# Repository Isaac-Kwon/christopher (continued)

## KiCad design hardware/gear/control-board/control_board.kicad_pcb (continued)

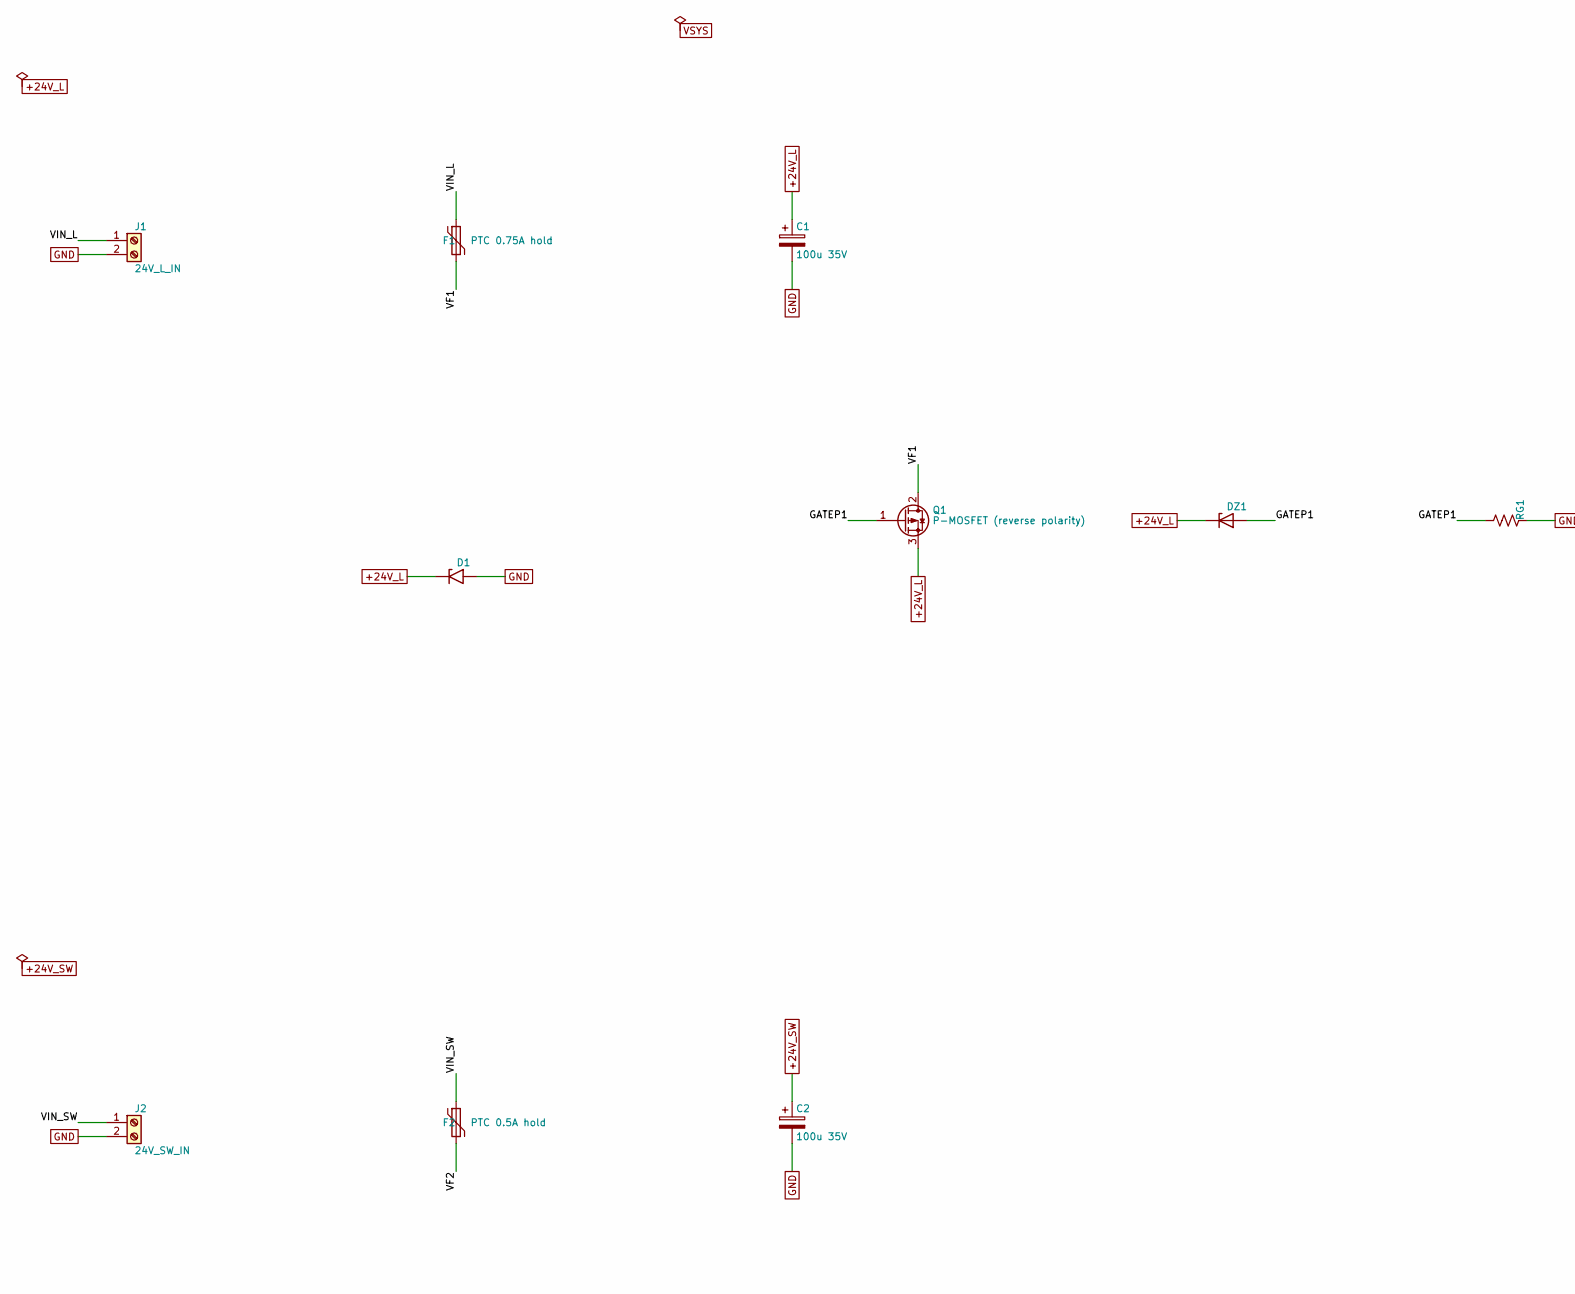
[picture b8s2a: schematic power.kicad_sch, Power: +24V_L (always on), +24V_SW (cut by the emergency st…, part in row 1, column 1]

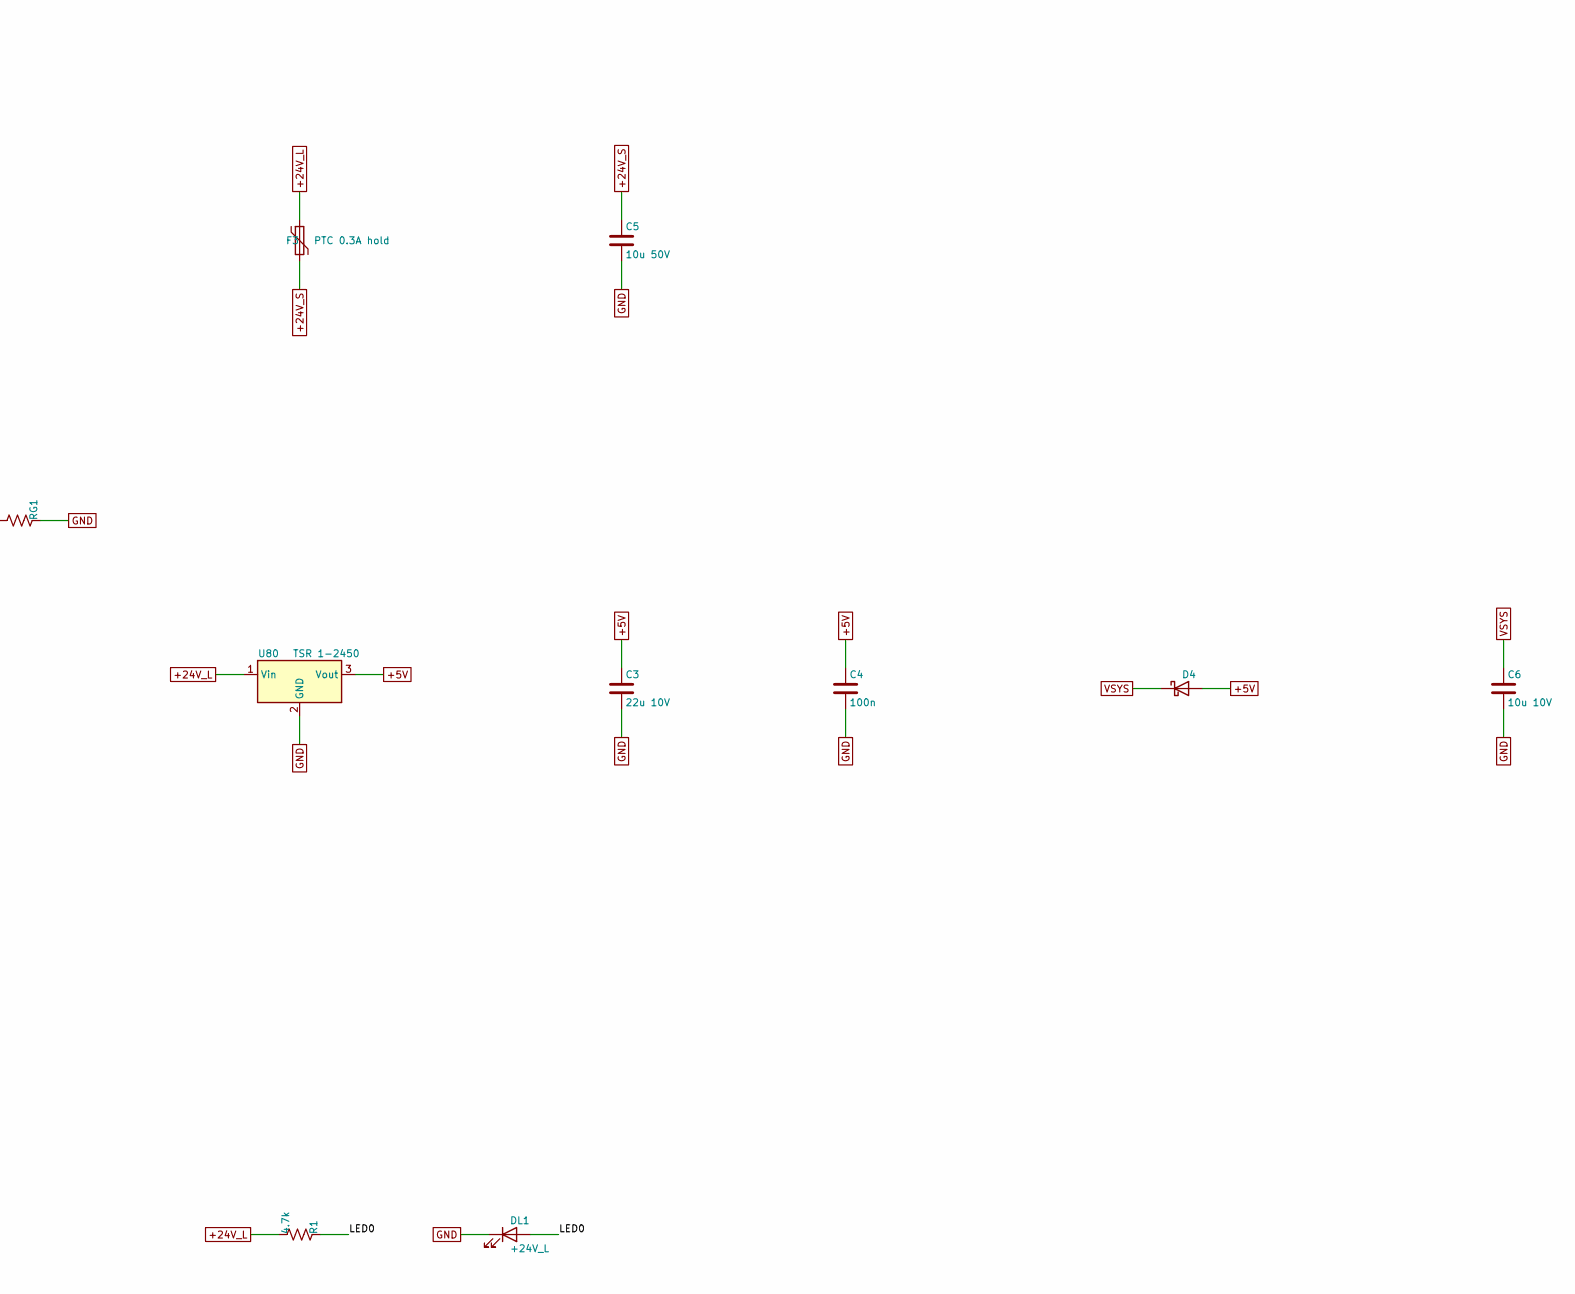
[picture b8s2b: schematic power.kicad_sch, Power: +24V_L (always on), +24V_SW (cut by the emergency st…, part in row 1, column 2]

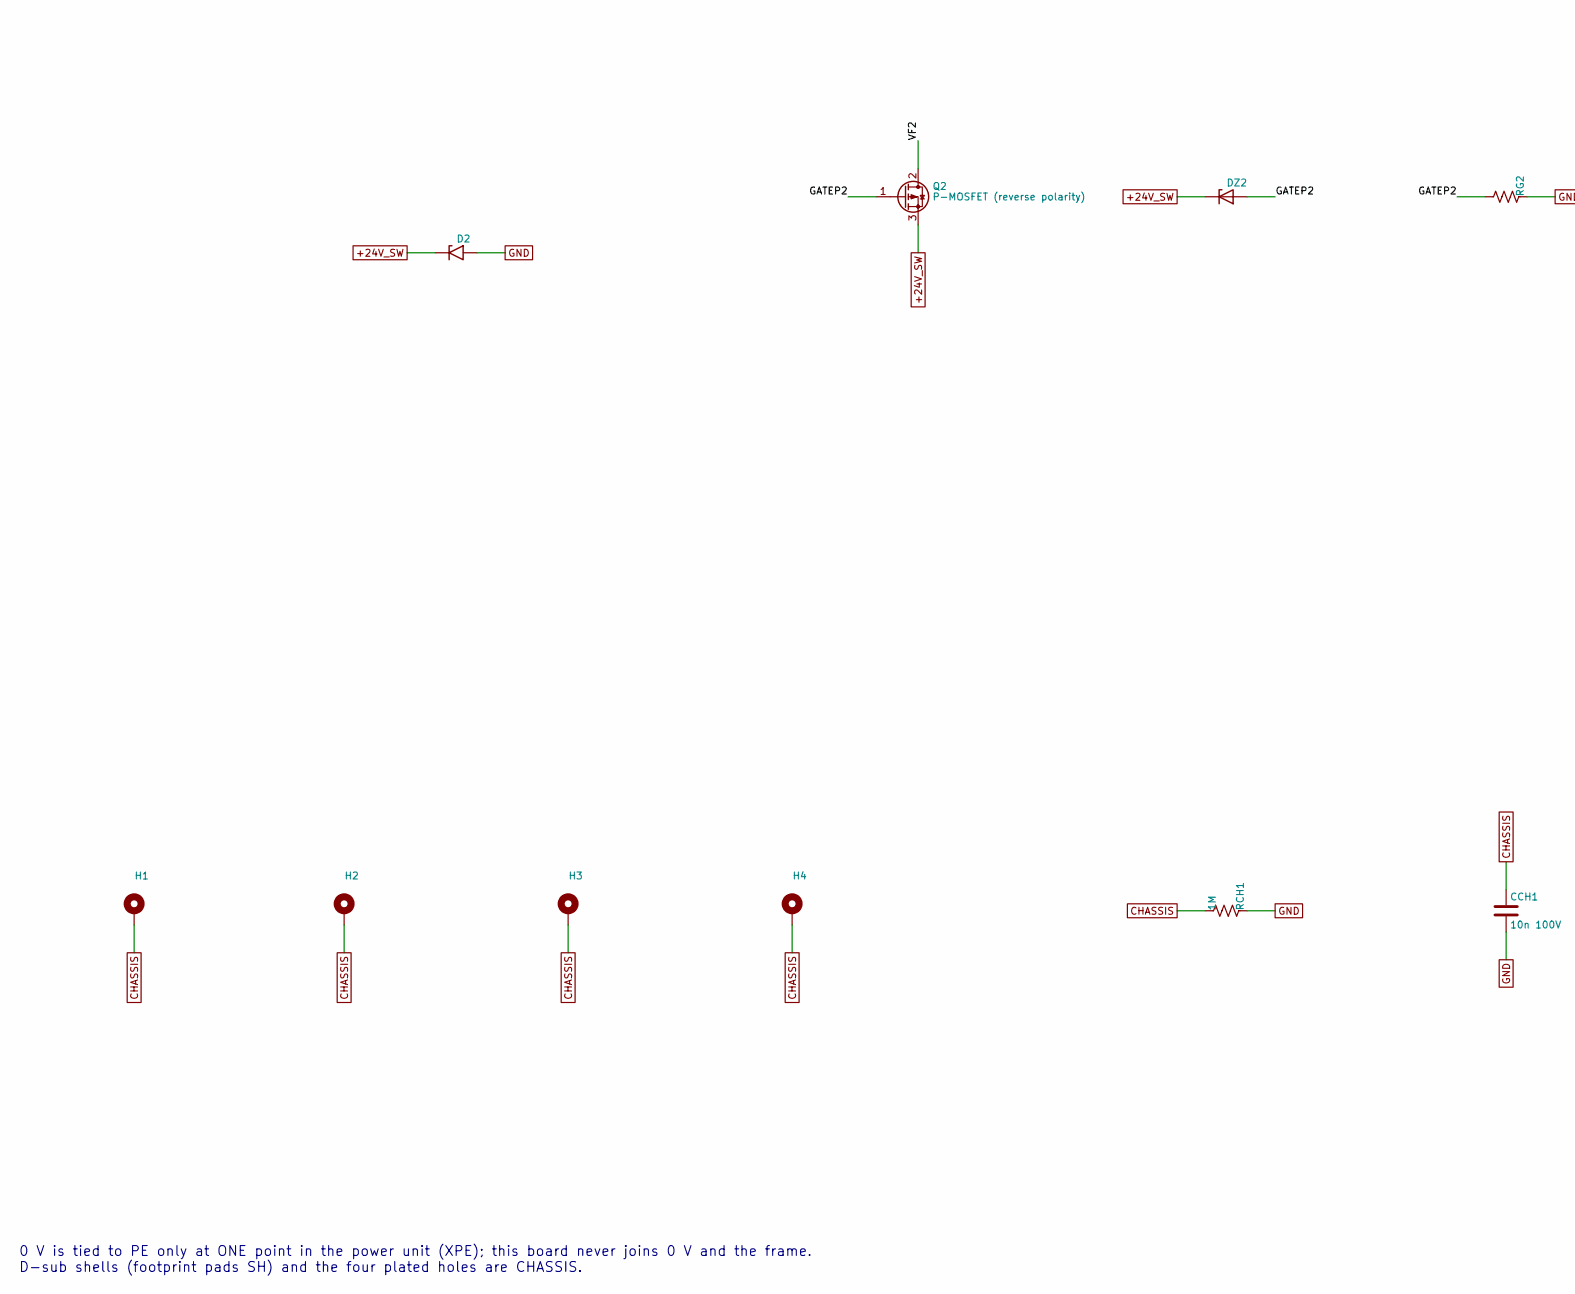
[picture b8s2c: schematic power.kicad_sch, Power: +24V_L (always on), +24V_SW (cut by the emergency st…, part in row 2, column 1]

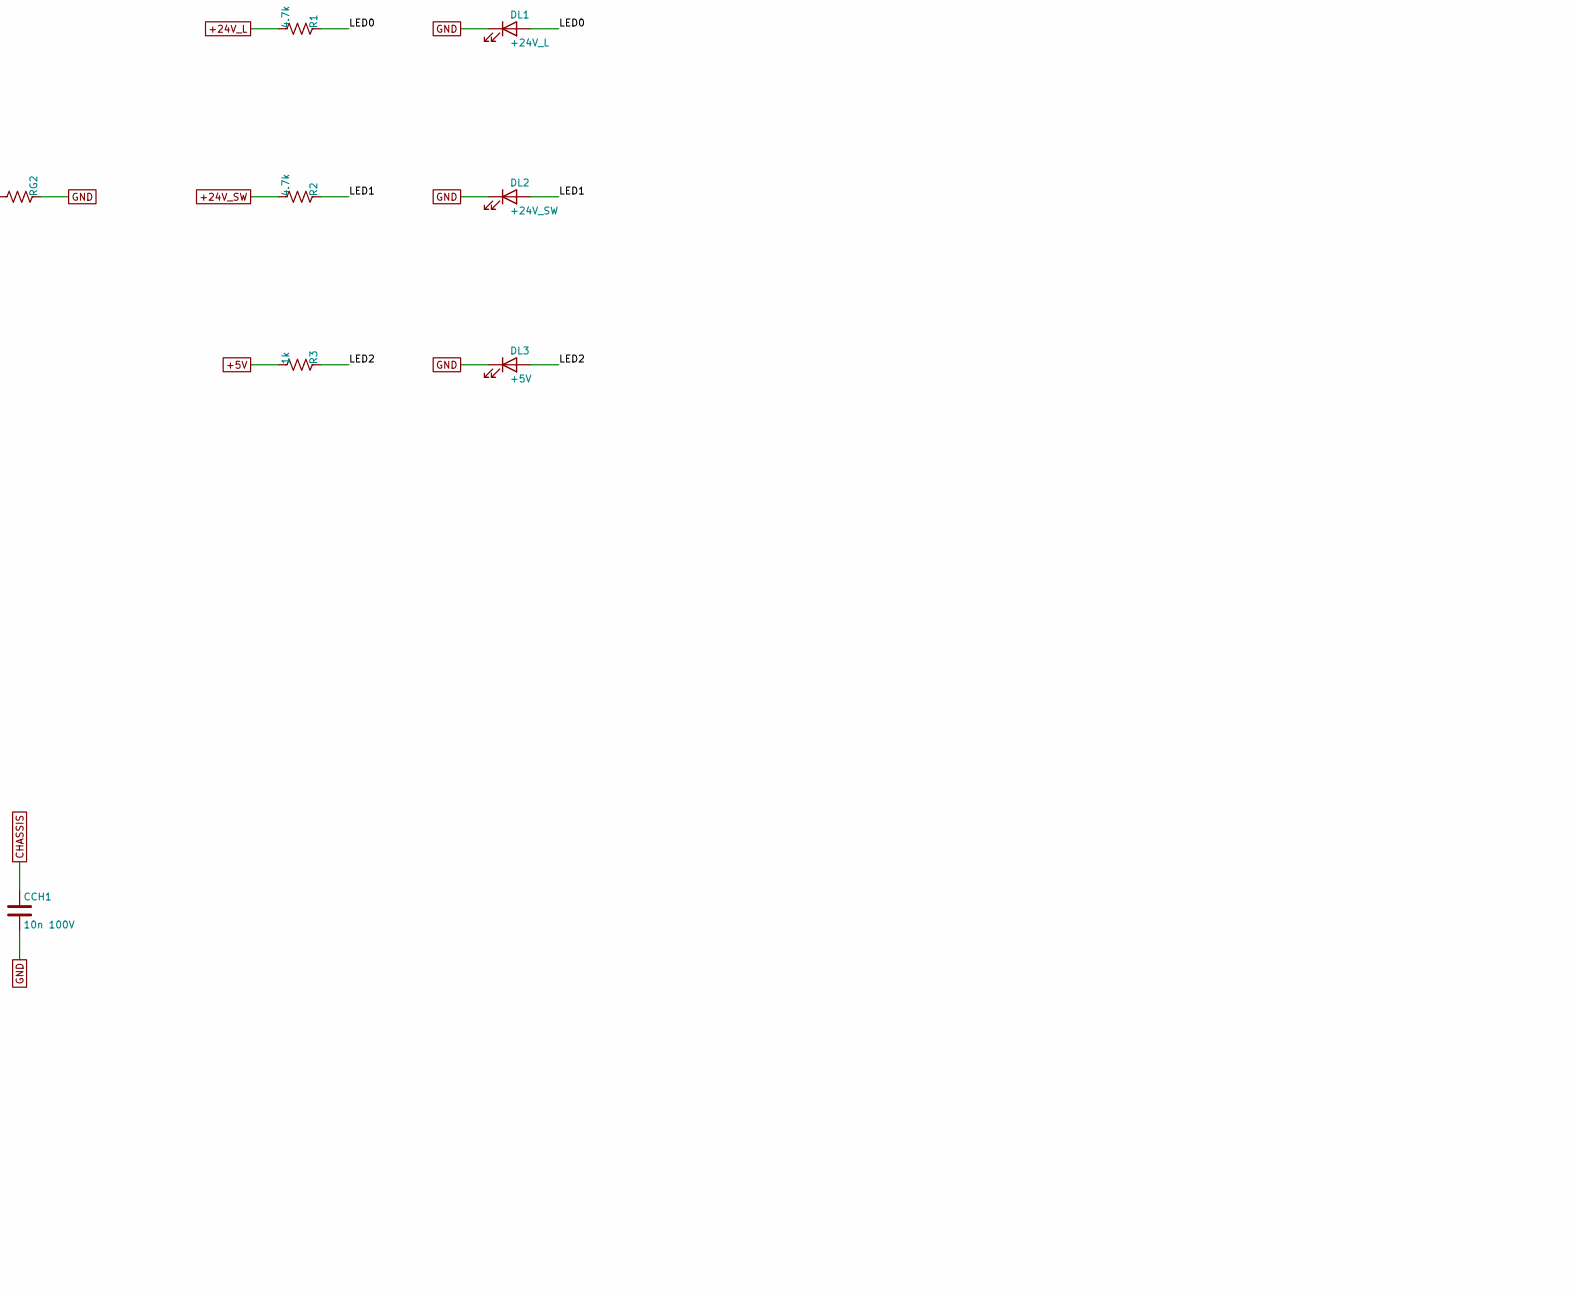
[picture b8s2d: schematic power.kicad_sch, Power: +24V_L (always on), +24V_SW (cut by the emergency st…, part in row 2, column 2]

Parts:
C1, C2: 100u 35V; CP_Elec_8x10
C3: 22u 10V; C_1206_3216Metric
C4: 100n; C_0603_1608Metric
C5: 10u 50V; C_1206_3216Metric
C6: 10u 10V; C_0805_2012Metric
CCH1: 10n 100V; C_0603_1608Metric
D1, D2: SMAJ33A; D_SMA
D4: SS14; D_SOD-123
DL1: +24V_L; LED_0603_1608Metric
DL2: +24V_SW; LED_0603_1608Metric
DL3: +5V; LED_0603_1608Metric
DZ1, DZ2: 12V; D_SOD-123
F1: PTC 0.75A hold; Fuse_1812_4532Metric
F2: PTC 0.5A hold; Fuse_1812_4532Metric
F3: PTC 0.3A hold; Fuse_1206_3216Metric
H1, H2, H3, H4: MountingHole_Pad; MountingHole_3.2mm_M3_Pad
J1: 24V_L_IN; TerminalBlock_Phoenix_MKDS-1,5-2-5.08_1x02_P5.08mm_Horizont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
J2: 24V_SW_IN; TerminalBlock_Phoenix_MKDS-1,5-2-5.08_1x02_P5.08mm_Horizont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
Q1, Q2: P-MOSFET (reverse polarity); SOT-223-3_TabPin2
R1, R2: 4.7k; R_0603_1608Metric
R3: 1k; R_0603_1608Metric
RCH1: 1M; R_0603_1608Metric
RG1, RG2: 100k; R_0603_1608Metric
U80: TSR 1-2450; Converter_DCDC_TRACO_TSR-1_THT

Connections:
+5V: C3.1, C4.1, D4.2 (A), R3.1, U80.3 (Vout)
+24V_L: C1.1, D1.1 (A1), DZ1.1 (K), F3.1, Q1.3 (S), R1.1, U80.1 (Vin); also elsewhere on the board
+24V_S: C5.1, F3.2; also elsewhere on the board
+24V_SW: C2.1, D2.1 (A1), DZ2.1 (K), Q2.3 (S), R2.1; also elsewhere on the board
/POWER/GATEP1: DZ1.2 (A), Q1.1 (G), RG1.1
/POWER/GATEP2: DZ2.2 (A), Q2.1 (G), RG2.1
/POWER/LED0: DL1.2 (A), R1.2
/POWER/LED1: DL2.2 (A), R2.2
/POWER/LED2: DL3.2 (A), R3.2
/POWER/VF1: F1.2, Q1.2 (D)
/POWER/VF2: F2.2, Q2.2 (D)
/POWER/VIN_L: F1.1, J1.1
/POWER/VIN_SW: F2.1, J2.1
CHASSIS: CCH1.1, H1.1, H2.1, H3.1, H4.1, RCH1.1; also elsewhere on the board
GND: C1.2, C2.2, C3.2, C4.2, C5.2, C6.2, CCH1.2, D1.2 (A2), D2.2 (A2), DL1.1 (K), DL2.1 (K), DL3.1 (K), J1.2, J2.2, RCH1.2, RG1.2, RG2.2, U80.2 (GND); also elsewhere on the board
VSYS: C6.1, D4.1 (K); also elsewhere on the board

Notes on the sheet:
0 V is tied to PE only at ONE point in the power unit (XPE); this board never joins 0 V and the frame. D-sub shells (footprint pads SH) and the four plated holes are CHASSIS.

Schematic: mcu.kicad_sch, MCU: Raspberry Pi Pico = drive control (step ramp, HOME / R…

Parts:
C10: 10u; C_0805_2012Metric
C11: 100n; C_0603_1608Metric
R10, R11, R12: 10k; R_0603_1608Metric
SW1: RESET; SW_SPST_PTS645Sx43SMTR92
U1: Raspberry Pi Pico; RaspberryPi_Pico_Common_THT

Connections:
+3V3: C10.1, C11.1, R11.2, R12.2, U1.36 (3V3); also elsewhere on the board
/MCU/RUN_PIN: SW1.1, U1.30 (RUN)
ALM_M: U1.17 (GPIO13); also elsewhere on the board
DIR_M: U1.2 (GPIO1); also elsewhere on the board
ENA_M: U1.4 (GPIO2); also elsewhere on the board
ESTOPOK_M: U1.20 (GPIO15); also elsewhere on the board
GND: C10.2, C11.2, R10.2, SW1.2, U1.3 (GND), U1.8 (GND), U1.13 (GND), U1.18 (GND), U1.23 (GND), U1.28 (GND), U1.38 (GND); also elsewhere on the board
HOME_M: U1.15 (GPIO11); also elsewhere on the board
HOMING: R11.1, U1.6 (GPIO4); also elsewhere on the board
ILOCKOK_M: U1.21 (GPIO16); also elsewhere on the board
I_L: U1.27 (GPIO21); also elsewhere on the board
I_M: U1.31 (GPIO26_ADC0); also elsewhere on the board
I_S: U1.34 (GPIO28_ADC2); also elsewhere on the board
MOSI_M: U1.9 (GPIO6); also elsewhere on the board
OE_M: R12.1, U1.11 (GPIO8); also elsewhere on the board
PUL_M: U1.1 (GPIO0); also elsewhere on the board
RCLK_M: U1.10 (GPIO7); also elsewhere on the board
RUN_M: U1.12 (GPIO9); also elsewhere on the board
SCK_M: U1.7 (GPIO5); also elsewhere on the board
SLOT_C: U1.25 (GPIO19); also elsewhere on the board
SLOT_J: U1.24 (GPIO18); also elsewhere on the board
SLOT_S: U1.22 (GPIO17); also elsewhere on the board
STOPL_M: U1.14 (GPIO10); also elsewhere on the board
SW_M: U1.19 (GPIO14); also elsewhere on the board
TXEN: R10.1, U1.5 (GPIO3); also elsewhere on the board
T_L: U1.26 (GPIO20); also elsewhere on the board
T_M: U1.29 (GPIO22); also elsewhere on the board
T_S: U1.32 (GPIO27_ADC1); also elsewhere on the board
V48_M: U1.16 (GPIO12); also elsewhere on the board
VSYS: U1.39 (VSYS); also elsewhere on the board

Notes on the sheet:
GP0 PUL GP1 DIR GP2 ENA (-> TBD62783A U60 -> 1.5k -> J_DRV) GP3 TXEN GP4 HOMING (-> LOGIC) GP5 SCK GP6 MOSI GP7 RCLK GP8 /OE -> 3 x 74HC595 (STOPPED, AT_HOME, END, POS0-14) GP9-16 RUN, STOP_LATCH, HOME, V48_OK, DRV_ALM, SW_OK, ESTOP_OK, ILOCK_OK (optocoupler outputs) GP17-19 conditioned slot levels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

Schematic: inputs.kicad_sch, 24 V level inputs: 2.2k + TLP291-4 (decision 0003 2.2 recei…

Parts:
D20, D21, D22, D23, D24, D25, D26, D27: 1N4148W; D_SOD-123
R20, R21, R22, R23, R24, R25, R26, R27: 2.2k; R_0603_1608Metric
R28: 4.7k; R_0603_1608Metric
R30, R31, R32, R33, R34, R35, R36, R37: 10k; R_0603_1608Metric
U40, U41: TLP291-4; SOIC-16_4.55x10.3mm_P1.27mm

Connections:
+3V3: U40.10, U40.12, U40.14, U40.16, U41.10, U41.12, U41.14, U41.16; also elsewhere on the board
+24V_L: R28.1; also elsewhere on the board
+24V_SW: R26.1; also elsewhere on the board
/INPUTS/SNS_ALM: D27.1 (K), R27.2, U41.7
/INPUTS/SNS_ESTOP_RET: D23.1 (K), R23.2, U40.7
/INPUTS/SNS_HOME: D22.1 (K), R22.2, U40.5
/INPUTS/SNS_ILOCK_RET: D24.1 (K), R24.2, U41.1
/INPUTS/SNS_RUN: D20.1 (K), R20.2, U40.1
/INPUTS/SNS_STOP_LATCH: D21.1 (K), R21.2, U40.3
/INPUTS/SNS_SW_OK: D26.1 (K), R26.2, U41.5
/INPUTS/SNS_V48_OK: D25.1 (K), R25.2, U41.3
ALM_IN: R27.1, R28.2; also elsewhere on the board
ALM_M: R37.1, U41.9; also elsewhere on the board
ESTOPOK_M: R33.1, U40.9; also elsewhere on the board
ESTOP_RET: R23.1; also elsewhere on the board
GND: D20.2 (A), D21.2 (A), D22.2 (A), D23.2 (A), D24.2 (A), D25.2 (A), D26.2 (A), D27.2 (A), R30.2, R31.2, R32.2, R33.2, R34.2, R35.2, R36.2, R37.2, U40.2, U40.4, U40.6, U40.8, U41.2, U41.4, U41.6, U41.8; also elsewhere on the board
HOME: R22.1; also elsewhere on the board
HOME_M: R32.1, U40.11; also elsewhere on the board
ILOCKOK_M: R34.1, U41.15; also elsewhere on the board
ILOCK_RET: R24.1; also elsewhere on the board
RUN: R20.1; also elsewhere on the board
RUN_M: R30.1, U40.15; also elsewhere on the board
STOPL_M: R31.1, U40.13; also elsewhere on the board
STOP_LATCH: R21.1; also elsewhere on the board
SW_M: R36.1, U41.11; also elsewhere on the board
V48_M: R35.1, U41.13; also elsewhere on the board
V48_OK: R25.1; also elsewhere on the board

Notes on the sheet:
Polarity: *_M = 1 when the 24 V input is high. ALM_M = 1 means the drive output is OPEN (alarm / drive unpowered). V48_OK: 24 V level from an a-type auxiliary contact of KM3 (the 48 V contactor); the power unit must supply it (open item).

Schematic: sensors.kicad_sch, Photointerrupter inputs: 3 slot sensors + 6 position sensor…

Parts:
C20, C21, C22, C23, C24, C25, C26, C27, C28: 4.7n; C_0603_1608Metric
J10: SENS_S; JST_XH_B3B-XH-A_1x03_P2.50mm_Vertical
J11: SENS_J; JST_XH_B3B-XH-A_1x03_P2.50mm_Vertical
J12: SENS_C; JST_XH_B3B-XH-A_1x03_P2.50mm_Vertical
J13: SENS_TL; JST_XH_B3B-XH-A_1x03_P2.50mm_Vertical
J14: SENS_IL; JST_XH_B3B-XH-A_1x03_P2.50mm_Vertical
J15: SENS_TM; JST_XH_B3B-XH-A_1x03_P2.50mm_Vertical
J16: SENS_IM; JST_XH_B3B-XH-A_1x03_P2.50mm_Vertical
J17: SENS_TS; JST_XH_B3B-XH-A_1x03_P2.50mm_Vertical
J18: SENS_IS; JST_XH_B3B-XH-A_1x03_P2.50mm_Vertical
R40, R41, R42, R43, R44, R45, R46, R47, R48: 4.7k; R_0603_1608Metric
R50, R51, R52, R53, R54, R55, R56, R57, R58: 1k; R_0603_1608Metric

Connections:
+3V3: R40.1, R41.1, R42.1, R43.1, R44.1, R45.1, R46.1, R47.1, R48.1; also elsewhere on the board
+24V_S: J10.1, J11.1, J12.1, J13.1, J14.1, J15.1, J16.1, J17.1, J18.1; also elsewhere on the board
/SENSORS/RAW_C: J12.2, R42.2, R52.1
/SENSORS/RAW_IL: J14.2, R44.2, R54.1
/SENSORS/RAW_IM: J16.2, R46.2, R56.1
/SENSORS/RAW_IS: J18.2, R48.2, R58.1
/SENSORS/RAW_J: J11.2, R41.2, R51.1
/SENSORS/RAW_S: J10.2, R40.2, R50.1
/SENSORS/RAW_TL: J13.2, R43.2, R53.1
/SENSORS/RAW_TM: J15.2, R45.2, R55.1
/SENSORS/RAW_TS: J17.2, R47.2, R57.1
FLT_C: C22.1, R52.2; also elsewhere on the board
FLT_IL: C24.1, R54.2; also elsewhere on the board
FLT_IM: C26.1, R56.2; also elsewhere on the board
FLT_IS: C28.1, R58.2; also elsewhere on the board
FLT_J: C21.1, R51.2; also elsewhere on the board
FLT_S: C20.1, R50.2; also elsewhere on the board
FLT_TL: C23.1, R53.2; also elsewhere on the board
FLT_TM: C25.1, R55.2; also elsewhere on the board
FLT_TS: C27.1, R57.2; also elsewhere on the board
GND: C20.2, C21.2, C22.2, C23.2, C24.2, C25.2, C26.2, C27.2, C28.2, J10.3, J11.3, J12.3, J13.3, J14.3, J15.3, J16.3, J17.3, J18.3; also elsewhere on the board

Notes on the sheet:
Slot windows (connector face, layout.md 3.8, CAD params.SLOT_STEPS): STROBE -2.50..+4.52 ms, JUDGE +8.56..+16.63, CLEAR +18.65..+31.73 at 60 rpm. STROBE calibration = rotating bracket of the STROBE sensor (decision 0002); nothing on the board.

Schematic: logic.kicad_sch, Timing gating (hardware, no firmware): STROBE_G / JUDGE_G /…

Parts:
C40, C41, C42, C43, C44, C45, C46, C47, C50: 100n; C_0603_1608Metric
C51: 10n; C_0603_1608Metric
R60: 100k; R_0603_1608Metric
R61: 47k; R_0603_1608Metric
U30, U31, U32: 74HC14; SOIC-14_3.9x8.7mm_P1.27mm
U33, U34: 74HC08; SOIC-14_3.9x8.7mm_P1.27mm
U35: 74HC32; SOIC-14_3.9x8.7mm_P1.27mm
U36: 74HC02; SOIC-14_3.9x8.7mm_P1.27mm
U37: 74HC74; SOIC-14_3.9x8.7mm_P1.27mm

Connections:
+3V3: C40.1, C41.1, C42.1, C43.1, C44.1, C45.1, C46.1, C47.1, R60.1, U30.14 (VCC), U31.14 (VCC), U32.14 (VCC), U33.14 (VCC), U34.14 (VCC), U35.14 (VCC), U36.14 (VCC), U37.2 (D), U37.4 (~S), U37.14 (VCC); also elsewhere on the board
CLEAR_G: U32.1, U33.6; also elsewhere on the board
CLR1: U35.6, U36.2, U36.5, U36.6
CLRN: U32.2, U37.11 (C)
CYC: U35.2, U37.9 (Q)
CYC_R_N: U36.4, U37.13 (~R)
FLT_C: U30.5; also elsewhere on the board
FLT_IL: U30.11; also elsewhere on the board
FLT_IM: U31.1; also elsewhere on the board
FLT_IS: U31.5; also elsewhere on the board
FLT_J: U30.3; also elsewhere on the board
FLT_S: U30.1; also elsewhere on the board
FLT_TL: U30.9; also elsewhere on the board
FLT_TM: U30.13; also elsewhere on the board
FLT_TS: U31.3; also elsewhere on the board
GND: C40.2, C41.2, C42.2, C43.2, C44.2, C45.2, C46.2, C47.2, C50.2, C51.2, U30.7 (GND), U31.7 (GND), U32.5, U32.7 (GND), U32.9, U32.11, U32.13, U33.7 (GND), U34.4, U34.5, U34.7 (GND), U34.9, U34.10, U34.12, U34.13, U35.7 (GND), U35.9, U35.10, U35.12, U35.13, U36.7 (GND), U36.8, U36.9, U36.11, U36.12, U37.7 (GND), U37.12 (D); also elsewhere on the board
HOMING: U35.5; also elsewhere on the board
I_L: U30.10; also elsewhere on the board
I_M: U31.2; also elsewhere on the board
I_S: U31.6; also elsewhere on the board
JUDGE_G: U33.11; also elsewhere on the board
JUDGE_X: U33.8, U33.12
POR: U31.12, U35.4
POR_RC: C50.1, R60.2, U31.13
SEEN: U33.10, U37.5 (Q)
SEEN_R_N: U36.1, U37.1 (~R)
SLOT_C: U30.6, U33.4; also elsewhere on the board
SLOT_J: U30.4, U33.9; also elsewhere on the board
SLOT_S: U30.2, U33.1; also elsewhere on the board
SL_D: C51.1, R61.2, U31.11
SL_DB: U31.10, U34.2
SL_N: R61.1, U31.8, U34.1
SL_PULSE: U34.3, U36.3
STOPL_M: U31.9; also elsewhere on the board
STROBE_G: U32.3, U33.3, U37.3 (C); also elsewhere on the board
STROBE_N: U32.4, U37.10 (~S)
TXE: U33.2, U33.5, U33.13, U35.3
TXEN: U35.1; also elsewhere on the board
T_L: U30.8; also elsewhere on the board
T_M: U30.12; also elsewhere on the board
T_S: U31.4; also elsewhere on the board

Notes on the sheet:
CYC ~S = STROBE_N (low while STROBE_G high), ~R = CYC_R_N = NOR(POR | HOMING) (power-up and HOME: a cycle cut by an emergency stop is dropped; the HOME flush CLEAR replaces its CLEAR), D = 0, clock = CLRN (rises when CLEAR_G falls). SEEN D = 1, clock = STROBE_G, ~R = SEEN_R_N = NOR(POR | HOMING, SL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

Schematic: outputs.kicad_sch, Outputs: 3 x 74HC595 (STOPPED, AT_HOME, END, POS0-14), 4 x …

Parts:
C60, C61, C62: 100n; C_0603_1608Metric
C70, C71, C72, C73: 100n 50V; C_0805_2012Metric
F20, F21, F22, F23, F24, F25, F26, F27, F28, F29, F30, F31, F32, F33, F34, F35, F36, F37, F38, F39, F40: PTC 30mA/100mA; Fuse_1206_3216Metric
R70, R71, R72, R73, R74, R75, R78, R79, R80, R81, R82, R83, R84, R85, R86, R87, R88, R89, R90, R91, R92, R93, R94, R95, R110, R111, R112, R113, R114, R115, R116, R117, R118, R119, R120, R121, R122, R123, R124, R125, R126, R127, R128, R129, R130: 47k; R_0603_1608Metric
R150, R151, R152: 1.5k; R_0603_1608Metric
U50, U51, U52: 74HC595; SOIC-16_3.9x9.9mm_P1.27mm
U60, U61, U62, U63: TBD62783APG; SOIC-18W_7.5x11.6mm_P1.27mm

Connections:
+3V3: C60.1, C61.1, C62.1, U50.10 (~SRCLR), U50.16 (VCC), U51.10 (~SRCLR), U51.16 (VCC), U52.10 (~SRCLR), U52.16 (VCC); also elsewhere on the board
+24V_L: C71.1, C72.1, C73.1, U61.9 (VCC), U62.9 (VCC), U63.9 (VCC); also elsewhere on the board
+24V_SW: C70.1, U60.9 (VCC); also elsewhere on the board
/OUTPUTS/CH0: U50.9 (QH'), U51.14 (SER)
/OUTPUTS/CH1: U51.9 (QH'), U52.14 (SER)
AT_HOME: F24.2, R114.1; also elsewhere on the board
BIT0: R78.1, U50.15 (QA), U61.1 (I1)
BIT1: R79.1, U50.1 (QB), U61.2 (I2)
BIT2: R80.1, U50.2 (QC), U61.3 (I3)
BIT3: R81.1, U50.3 (QD), U61.4 (I4)
BIT4: R82.1, U50.4 (QE), U61.5 (I5)
BIT5: R83.1, U50.5 (QF), U61.6 (I6)
BIT6: R84.1, U50.6 (QG), U61.7 (I7)
BIT7: R85.1, U50.7 (QH), U61.8 (I8)
BIT8: R86.1, U51.15 (QA), U62.1 (I1)
BIT9: R87.1, U51.1 (QB), U62.2 (I2)
BIT10: R88.1, U51.2 (QC), U62.3 (I3)
BIT11: R89.1, U51.3 (QD), U62.4 (I4)
BIT12: R90.1, U51.4 (QE), U62.5 (I5)
BIT13: R91.1, U51.5 (QF), U62.6 (I6)
BIT14: R92.1, U51.6 (QG), U62.7 (I7)
BIT15: R93.1, U51.7 (QH), U62.8 (I8)
BIT16: R94.1, U52.15 (QA), U63.1 (I1)
BIT17: R95.1, U52.1 (QB), U63.2 (I2)
CLEAR: F22.2, R112.1; also elsewhere on the board
CLEAR_G: R72.1, U60.3 (I3); also elsewhere on the board
DIR_M: R74.1, U60.5 (I5); also elsewhere on the board
DO_AT_HOME: F24.1, U61.17 (O2)
DO_CLEAR: F22.1, U60.16 (O3)
DO_DIR: R151.1, U60.14 (O5)
DO_ENA: R152.1, U60.13 (O6)
DO_END: F25.1, U61.16 (O3)
DO_JUDGE: F21.1, U60.17 (O2)
DO_POS0: F26.1, U61.15 (O4)
DO_POS1: F27.1, U61.14 (O5)
DO_POS2: F28.1, U61.13 (O6)
DO_POS3: F29.1, U61.12 (O7)
DO_POS4: F30.1, U61.11 (O8)
DO_POS5: F31.1, U62.18 (O1)
DO_POS6: F32.1, U62.17 (O2)
DO_POS7: F33.1, U62.16 (O3)
DO_POS8: F34.1, U62.15 (O4)
DO_POS9: F35.1, U62.14 (O5)
DO_POS10: F36.1, U62.13 (O6)
DO_POS11: F37.1, U62.12 (O7)
DO_POS12: F38.1, U62.11 (O8)
DO_POS13: F39.1, U63.18 (O1)
DO_POS14: F40.1, U63.17 (O2)
DO_PUL: R150.1, U60.15 (O4)
DO_STOPPED: F23.1, U61.18 (O1)
DO_STROBE: F20.1, U60.18 (O1)
DRV_DIR: R151.2; also elsewhere on the board
DRV_ENA: R152.2; also elsewhere on the board
DRV_PUL: R150.2; also elsewhere on the board
ENA_M: R75.1, U60.6 (I6); also elsewhere on the board
END: F25.2, R115.1; also elsewhere on the board
GND: C60.2, C61.2, C62.2, C70.2, C71.2, C72.2, C73.2, R70.2, R71.2, R72.2, R73.2, R74.2, R75.2, R78.2, R79.2, R80.2, R81.2, R82.2, R83.2, R84.2, R85.2, R86.2, R87.2, R88.2, R89.2, R90.2, R91.2, R92.2, R93.2, R94.2, R95.2, R110.2, R111.2, R112.2, R113.2, R114.2, R115.2, R116.2, R117.2, R118.2, R119.2, R120.2, R121.2, R122.2, R123.2, R124.2, R125.2, R126.2, R127.2, R128.2, R129.2, R130.2, U50.8 (GND), U51.8 (GND), U52.8 (GND), U60.7 (I7), U60.8 (I8), U60.10 (GND), U61.10 (GND), U62.10 (GND), U63.3 (I3), U63.4 (I4), U63.5 (I5), U63.6 (I6), U63.7 (I7), U63.8 (I8), U63.10 (GND); also elsewhere on the board
JUDGE: F21.2, R111.1; also elsewhere on the board
JUDGE_G: R71.1, U60.2 (I2); also elsewhere on the board
MOSI_M: U50.14 (SER); also elsewhere on the board
OE_M: U50.13 (~OE), U51.13 (~OE), U52.13 (~OE); also elsewhere on the board
POS0: F26.2, R116.1; also elsewhere on the board
POS1: F27.2, R117.1; also elsewhere on the board
POS2: F28.2, R118.1; also elsewhere on the board
POS3: F29.2, R119.1; also elsewhere on the board
POS4: F30.2, R120.1; also elsewhere on the board
POS5: F31.2, R121.1; also elsewhere on the board
POS6: F32.2, R122.1; also elsewhere on the board
POS7: F33.2, R123.1; also elsewhere on the board
POS8: F34.2, R124.1; also elsewhere on the board
POS9: F35.2, R125.1; also elsewhere on the board
POS10: F36.2, R126.1; also elsewhere on the board
POS11: F37.2, R127.1; also elsewhere on the board
POS12: F38.2, R128.1; also elsewhere on the board
POS13: F39.2, R129.1; also elsewhere on the board
POS14: F40.2, R130.1; also elsewhere on the board
PUL_M: R73.1, U60.4 (I4); also elsewhere on the board
RCLK_M: U50.12 (RCLK), U51.12 (RCLK), U52.12 (RCLK); also elsewhere on the board
SCK_M: U50.11 (SRCLK), U51.11 (SRCLK), U52.11 (SRCLK); also elsewhere on the board
STOPPED: F23.2, R113.1; also elsewhere on the board
STROBE: F20.2, R110.1; also elsewhere on the board
STROBE_G: R70.1, U60.1 (I1); also elsewhere on the board

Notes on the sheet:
DRV_PUL / DRV_DIR / DRV_ENA = 24 V high-side (+24V_SW) through 1.5k to the drive terminal J_DRV; PUL-, DIR-, ENA- are tied to 0 V at the drive. Pulses: 400 per position = 2600 per motor revolution (4:1 belt, 26 positions per F axis revolution) (calculated).

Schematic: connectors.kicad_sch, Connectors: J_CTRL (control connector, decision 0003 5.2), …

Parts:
J3: J_CTRL; DSUB-37_Pins_Horizontal_P2.77x2.84mm_EdgePinOffset9.90mm_Ho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
J4: J_SAFE; TerminalBlock_Phoenix_MKDS-1,5-6-5.08_1x06_P5.08mm_Horizont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
J5: J_DRV; TerminalBlock_Phoenix_MKDS-1,5-6-5.08_1x06_P5.08mm_Horizont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
J6: J_AUX; TerminalBlock_Phoenix_MKDS-1,5-2-5.08_1x02_P5.08mm_Horizont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
J7: TP_SLOT; PinHeader_1x04_P2.54mm_Vertical
SJ1: ESTOP SRC-A (bridged); SolderJumper-2_P1.3mm_Bridged_RoundedPad1.0x1.5mm
SJ2: ILOCK SRC-A (open); SolderJumper-2_P1.3mm_Open_RoundedPad1.0x1.5mm
SJ3: ILOCK CH-A (bridged); SolderJumper-2_P1.3mm_Bridged_RoundedPad1.0x1.5mm
SJ4: ESTOP K (bridged); SolderJumper-2_P1.3mm_Bridged_RoundedPad1.0x1.5mm
SJ5: ILOCK K (bridged); SolderJumper-2_P1.3mm_Bridged_RoundedPad1.0x1.5mm

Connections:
ALM_IN: J5.5; also elsewhere on the board
AT_HOME: J3.5; also elsewhere on the board
CHASSIS: J3.SH; also elsewhere on the board
CLEAR: J3.35; also elsewhere on the board
DRV_DIR: J5.2; also elsewhere on the board
DRV_ENA: J5.3; also elsewhere on the board
DRV_PUL: J5.1; also elsewhere on the board
END: J3.6; also elsewhere on the board
ESTOP_A: J3.22, SJ1.2 (B)
ESTOP_K: J4.4, SJ4.2 (B)
ESTOP_RET: J3.23, SJ4.1 (A); also elsewhere on the board
ESTOP_SRC: J4.1, SJ1.1 (A)
GND: J3.28, J3.29, J3.30, J3.31, J3.32, J3.33, J4.6, J5.4, J5.6, J6.2, J7.4; also elsewhere on the board
HOME: J3.4; also elsewhere on the board
ILOCK_A: J3.24, SJ2.2 (B), SJ3.2 (B)
ILOCK_CH: J4.3, SJ3.1 (A)
ILOCK_K: J4.5, SJ5.2 (B)
ILOCK_RET: J3.25, SJ5.1 (A); also elsewhere on the board
ILOCK_SRC: J4.2, SJ2.1 (A)
JUDGE: J3.34; also elsewhere on the board
POS0: J3.7; also elsewhere on the board
POS1: J3.8; also elsewhere on the board
POS2: J3.9; also elsewhere on the board
POS3: J3.10; also elsewhere on the board
POS4: J3.11; also elsewhere on the board
POS5: J3.12; also elsewhere on the board
POS6: J3.13; also elsewhere on the board
POS7: J3.14; also elsewhere on the board
POS8: J3.15; also elsewhere on the board
POS9: J3.16; also elsewhere on the board
POS10: J3.17; also elsewhere on the board
POS11: J3.18; also elsewhere on the board
POS12: J3.19; also elsewhere on the board
POS13: J3.20; also elsewhere on the board
POS14: J3.21; also elsewhere on the board
RUN: J3.2; also elsewhere on the board
SLOT_C: J7.3; also elsewhere on the board
SLOT_J: J7.2; also elsewhere on the board
SLOT_S: J7.1; also elsewhere on the board
STOPPED: J3.3; also elsewhere on the board
STOP_LATCH: J3.36; also elsewhere on the board
STROBE: J3.1; also elsewhere on the board
V48_OK: J6.1; also elsewhere on the board

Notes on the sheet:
Safety-loop pins are bank-owned (0003 4.6): K_E / K_I sit in the power unit; the board only passes the loop through J_CTRL and reads the returns. A cable pulled out from J_CTRL opens both loops.

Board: 4 copper layers, 216 parts (0 on the bottom side), 170 nets, no tracks yet.
